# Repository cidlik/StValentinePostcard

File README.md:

# Идея

Сделать валентинку в виде печатной платы с микроконтроллером и светодиодами. Должна работать от
часовой батарейки. Основные пункты:

* должна быть дешевой;
* должно быть минимум компонентов (см. предыдущий пункт);
* должна быть низкопотребляющей;
* все компоненты, кроме светодиодов и кнопки, должны быть на обратной стороне платы.

Эскиз на рисунке ниже:

<figure style="text-align: center">
	
	<figcaption style="text-align: center">Эскиз устройства</figcaption>
</figure>

# Выбор светодиодов

Основные варианты:

* Обычные светодиоды, например, [TO-1608BC-MRE](https://www.chipdip.ru/product/to-1608bc-mre-svetodiod-krasnyy-smd-1608-112mkd-oasistek-9000414317):

    * (+) дешево
    * (+) энергоэффективно
    * (-) нужно много ног для управления
    * (-) сердито
    * Параметры:

        * Прямой ток 25 мА;
        * Прямое напряжение 2 В.

* Адресный, например, [SK(C)6812-RGBW-BW](https://www.chipdip.ru/product/sk-c-6812-rgbw-bw-neopixel-svetodiod-shenzhen-shiningled-9000373823):

    * (+) красиво, много режимов
    * (+) всего 2 провода для управления
    * (-) скорее всего будет больше жрать, хотя как запрограммировать
    * (-) борьба с наводками???
    * (-) дороже
    * Параметры:

        * Напряжение питания 3.7-5.5 В
        * Прямой ток 20-30 мА на один цвет.

# Оценка потребления

Выбираются 14 светодиодов TO-1608BC-MRE. Ток ограничивается до 15 мА через резистор. Режимы:

1. Один светодиод в единицу времени;
2. Все светодиоды разом (худший случай).

Для первого режима потребление по светодиодам 15 мА. Для второго - 15 * 14 = 210 мА.

Пусть будет _какая-то_ батарейка на 100 мАч (см. [таблицу](https://mosclock.ru/clock/o-garantii/zamena-batareek/tablitsa-sravneniya-chasovykh-batareek/?srsltid=AfmBOorHNBOLRriNnmurLrfbC0cLY0ivmhHh0GXlCDRKjwAtHPy7bsK3)). Тогда 

1. 100 / 15 ~= 6 ч на одни только светодиоды;
2. 100 / 210 ~= 0.5 ч на одни только светодиоды.

# Выбор микроконтроллера

Судя по всему, это будет STM32L0. Варианты:

1. [STM32L011F3P6](https://www.chipdip.ru/product/stm32l011f3p6-st-microelectronics-8003145100)
2. [STM32L010F4P6](https://www.chipdip.ru/product/stm32l010f4p6-mikrokontroller-arm-st-microelectronics-9001089803)

Почему STM:

* знаю, что там точно есть режимы с супер низким потреблением;
* знакомая платформа;
* не нужно будет докупать программатор, т.к. он есть.

Вариант 1:

* Корпус: TSSOP-20
* GPIO: 11-15 (зависит от того, что смогу сконфигурировать)
* Напряжение питания от 1.65 до 3.6 В.
* Тактирование от внутренней RC-цепочки.

Вариант 2 не рассматривается, т.к. 1-й вариант более чем устраивает.

# Что говорит ИИ?

* [Ответ 1](https://share.google/aimode/JZRhZsYDs94hqZSMV).
* [Ответ 2](https://share.google/aimode/ylKgjJaCaAhDsedJH).

# Выбор батарейки

Судя по всему, подходит [CR2032](https://www.dart.ru/cataloguenew/others/accumulator/html/cr2032.shtml).
Характеристики:

* выходное напряжение 3 В;
* выходной ток  0.4 мА;
* мощность 210 мА/ч.

# Блок-схема устройства

<figure style="text-align: center">
	
	<figcaption style="text-align: center">Блок-схема устройства</figcaption>
</figure>

# Попытка рассчитать буферный конденсатор

Потребляемая мощность:

$$ P = P_{mc} + P_d $$

где $P_{mc}$ - мощность, потребляемая МК, $P_d$ - мощность, рассеиваемая при зажигании одного
светодиода.

Требуется определить количество энергии, которое будет потреблено за 1 секунду. Оцениваем мощности:

* $ P_d = I^2 \cdot R = 0.015^2 \cdot 120 = 0.027 $ Вт;
* $ P_{mc} = 3 \cdot 0.0005 = 0.0015 $ Вт (грубая оценка, судя по всему не должно превышать этого значения, см.
"Table 22. Current consumption in Run mode, code with data processing running from Flash" для MSI
clock).

Тогда

$$ E = (0.027 + 0.0015) \cdot 1 = 0.0285\ Дж $$

Энергия конденсатора определяется выражением:

$$ E_c = {CU^2 \over 2} $$

Определяем разницу энергий - до включения светодиода и после выключения. Допустим, что напряжение
$U_{low}$ может упасть до 2 В. Эта разница - та энергия, которая уходит на микроконтроллер и на
горение светодиода. Тогда ёмкость:

$$ C = {2E \over U_0^2 - U_{low}^2} = {2 \cdot 0.0285 \over 3^2 - 2^2} = 0.0114\ Ф = 11400\ мкФ $$

Это при условии, что светодиод будет постоянно гореть, а микроконтроллер не будет переводиться в
низкопотребляющие режимы.

Пусть светодиод будет гореть 5% от всего времени, тогда $P_d = 0.027 \cdot 0.05 = 0.00135\ Вт$.
Тогда ёмкость:

$$ C = {2 \cdot (0.0015 + 0.00135) \over 3^2 - 2^2} = 1140\ мкФ$$

# Схема электрическая принципиальная

<figure style="text-align: center">
	
	<figcaption style="text-align: center">Схема электрическая принципиальная</figcaption>
</figure>

# Алгоритм сборки

* Пайка резисторов для светодиодов на нижней стороне платы: флюс, паста, установить резисторы,
  прогреть феном. После операции проверить мультиметром пайку (у каждого резистора есть переходное
  отверстие, использовать его и КП микроконтроллера).
  **Внимание!** R12 и R11 не запаивать!
* Пайка светодиодов на верхней стороне платы: флюс, паста, установить светодиоды, прогреть феном.
  После операции проверить мультиметром пайку (у каждого светодиода есть переходное отверстие,
  использовать его и землю).
* Пайка микроконтроллера: флюс, запаять паяльником краевые выводы. Затем движениями от МК до конца
  площадки нанести припой. После пайки проверить все линии. Проверить, нет ли КЗ по всем линиям.
* Запаять R15.
* Пайка кнопки. Кнопка размещается с верхней стороны. После установки в посадочное место обрезать
  выводы с другой стороны и запаять.
* Прошить МК прошивкой с флагом DEBUG, убедиться, что все ок.
* Прошить МК прошивкой без флага DEBUG.
* Запаять R12 и R11.
* Пайка конденсаторов (вывод с полосой - gnd). ~~Предположительно хватит 2-х конденсаторов~~
  Поставил все 3. Конденсаторы - с нижней стороны. После установки в посадочное   место обрезать
  выводы с другой стороны и запаять.
* Отчистить плату.
* Запаять отсек для батарейки и включить устройство.
* Зашкурить

# Итоговое потребление

* STATE_START: 380 мА (ничего не мигает)
* STATE_RUNNING_LED: 850 мА
* STATE_SYMMETRY_RUNNING_LED: 880 мА

Просадок напряжения питания осциллографом не увидел.

# Что можно улучшить?

## Конструктивно

* Вывести площадку с NRST, чтобы можно было не бояться закирпичить устройство.
* Добавить запаиваемую перемычку после R15, чтобы можно было более удобно измерять силу тока.
* Не забыть шелкографию при производстве плат))0))
* Выбрать какие-то другие светодиоды. Паять эти - сущий ад.

  * Возможно имеет смысл поставить низкопотребляющие светодиоды.

* Сделать площадки светодиодов и резисторов побольше чуть-чуть.
* Исправить посадочное место J1 - сейчас шаг маленький, не могу поставить стандартный PLS.
* Конденсатор после кнопки для фильтрации дребезга.
* Поставить запаиваемые перемычки на линиях LED10 и LED11, чтобы можно было паять сразу все резисторы. Тогда проблем с прошивкой быть не должно.

## Программно

* Улучшить реализацию фильтра дребезга.
* Добавить больше режимов.
* Поддержать Stop и Standby режимы.
* Более тонко понастраивать потребление через задержки.
* Использовать LSI вместо HSI16.

# Итоги

* Устройство заработало.

<figure style="text-align: center">
	
	<figcaption style="text-align: center">Результат. Передняя сторона</figcaption>
</figure>

<figure style="text-align: center">
	
	<figcaption style="text-align: center">Результат. Задняя сторона</figcaption>
</figure>

<figure style="text-align: center">
	
	<figcaption style="text-align: center">Результат в действии</figcaption>
</figure>

* Дешевым проект не назову - платы дорого вышли. Но делал срочный заказ, чтобы успеть к сроку, так
  что пойдет.

* Требование по низкому потреблению выдержано, можно улучшить.

# Для справки

* Светодиоды с низким током потребления:

    * [led smd 1ma](https://www.chipdip.ru/search?searchtext=led+smd+1ma)
    * [VLMA3100-GS08](https://www.chipdip.ru/product/vlma3100-gs08-led-yellow-smd-plcc-2-2-ma-2.2-v-594-vishay-8733971327)

# Полезные ссылки

* [Basics of power supply design for MCU](https://wiki.st.com/stm32mcu/wiki/Basics_of_power_supply_design_for_MCU)
* [Краткое руководство KiCad](https://docs.kicad.org/5.1/ru/getting_started_in_kicad/getting_started_in_kicad.html)
* [Ultra Low Power LED Flasher using the Padauk PFS154](https://cpldcpu.com/2021/02/07/ultra-low-power-led-flasher/)
* [Про буферные конденсаторы](https://habr.com/ru/articles/671232/)

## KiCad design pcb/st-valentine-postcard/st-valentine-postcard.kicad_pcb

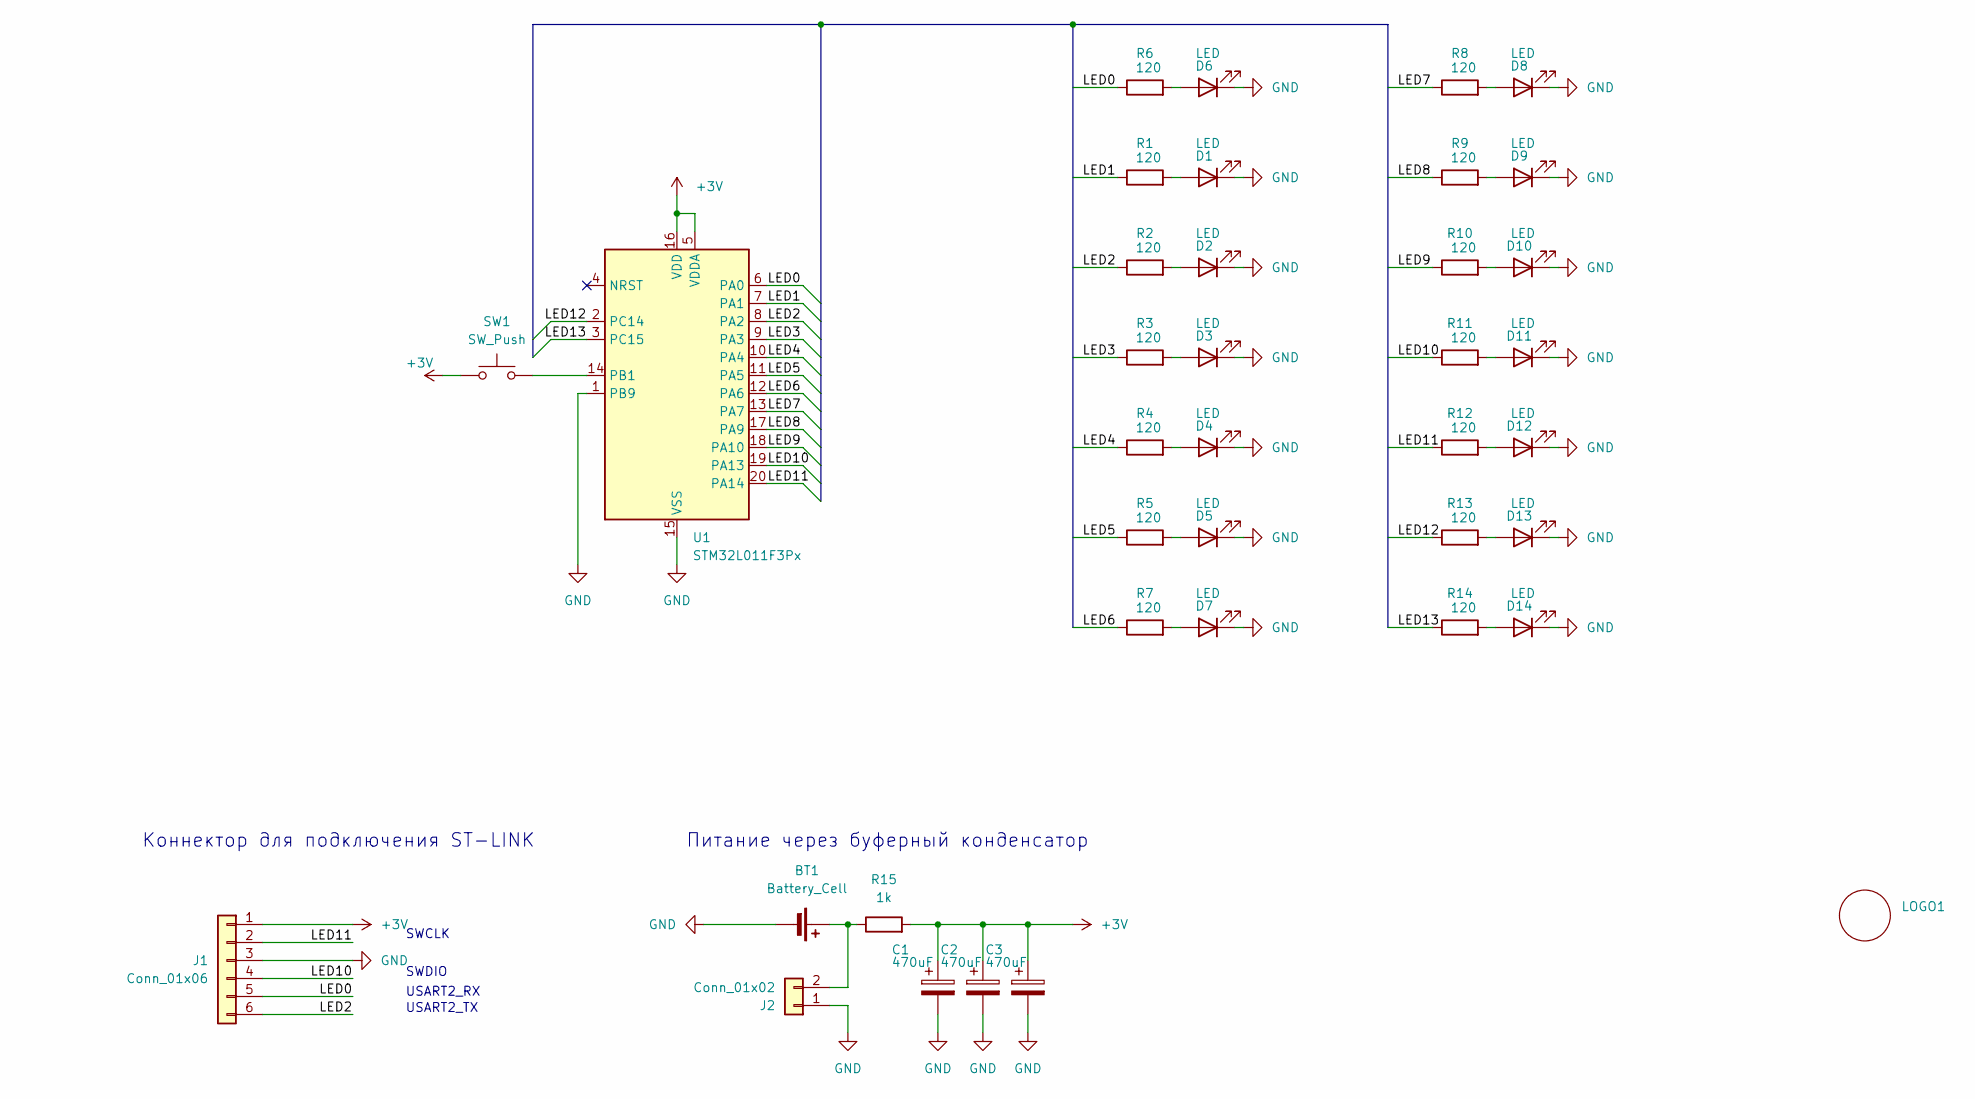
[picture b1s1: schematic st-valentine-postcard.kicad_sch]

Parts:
BT1: Battery_Cell; BatteryHolder_KLS5_CR2032_01
C1, C2, C3: 470uF; C_Radial_D6.3mm_H7.0mm_P2.50mm
D1, D2, D3, D4, D5, D6, D7, D8, D9, D10, D11, D12, D13, D14: LED; D_0201_0603Metric
J1: Conn_01x06; PinHeader_1x06_P2.00mm_Vertical
J2: Conn_01x02; PinHeader_1x02_P2.54mm_Vertical
LOGO1: cdk_logo_6x6mm
R1, R2, R3, R4, R5, R6, R7, R8, R9, R10, R11, R12, R13, R14: 120; R_0201_0603Metric_1.6x0.8
R15: 1k; R_0201_0603Metric_1.6x0.8
SW1: SW_Push; SW_PUSH_6mm_H4.3mm
U1: STM32L011F3Px; TSSOP-20_4.4x6.5mm_P0.65mm

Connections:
+3V: C1.1, C2.1, C3.1, J1.1, R15.2, SW1.1, U1.5 (VDDA), U1.16 (VDD)
/LED0: J1.5, R6.1, U1.6 (PA0)
/LED1: R1.1, U1.7 (PA1)
/LED2: J1.6, R2.1, U1.8 (PA2)
/LED3: R3.1, U1.9 (PA3)
/LED4: R4.1, U1.10 (PA4)
/LED5: R5.1, U1.11 (PA5)
/LED6: R7.1, U1.12 (PA6)
/LED7: R8.1, U1.13 (PA7)
/LED8: R9.1, U1.17 (PA9)
/LED9: R10.1, U1.18 (PA10)
/LED10: J1.4, R11.1, U1.19 (PA13)
/LED11: J1.2, R12.1, U1.20 (PA14)
/LED12: R13.1, U1.2 (PC14)
/LED13: R14.1, U1.3 (PC15)
GND: BT1.2 (-), C1.2, C2.2, C3.2, D1.1 (K), D2.1 (K), D3.1 (K), D4.1 (K), D5.1 (K), D6.1 (K), D7.1 (K), D8.1 (K), D9.1 (K), D10.1 (K), D11.1 (K), D12.1 (K), D13.1 (K), D14.1 (K), J1.3, J2.1, U1.1 (PB9), U1.15 (VSS)
unnamed: BT1.1 (+), J2.2, R15.1
unnamed: D1.2 (A), R1.2
unnamed: D2.2 (A), R2.2
unnamed: D3.2 (A), R3.2
unnamed: D4.2 (A), R4.2
unnamed: D5.2 (A), R5.2
unnamed: D6.2 (A), R6.2
unnamed: D7.2 (A), R7.2
unnamed: D8.2 (A), R8.2
unnamed: D9.2 (A), R9.2
unnamed: D10.2 (A), R10.2
unnamed: D11.2 (A), R11.2
unnamed: D12.2 (A), R12.2
unnamed: D13.2 (A), R13.2
unnamed: D14.2 (A), R14.2
unnamed: SW1.2, U1.14 (PB1)

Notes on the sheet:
USART2_TX
Коннектор для подключения ST-LINK
SWDIO
USART2_RX
SWCLK
Питание через буферный конденсатор

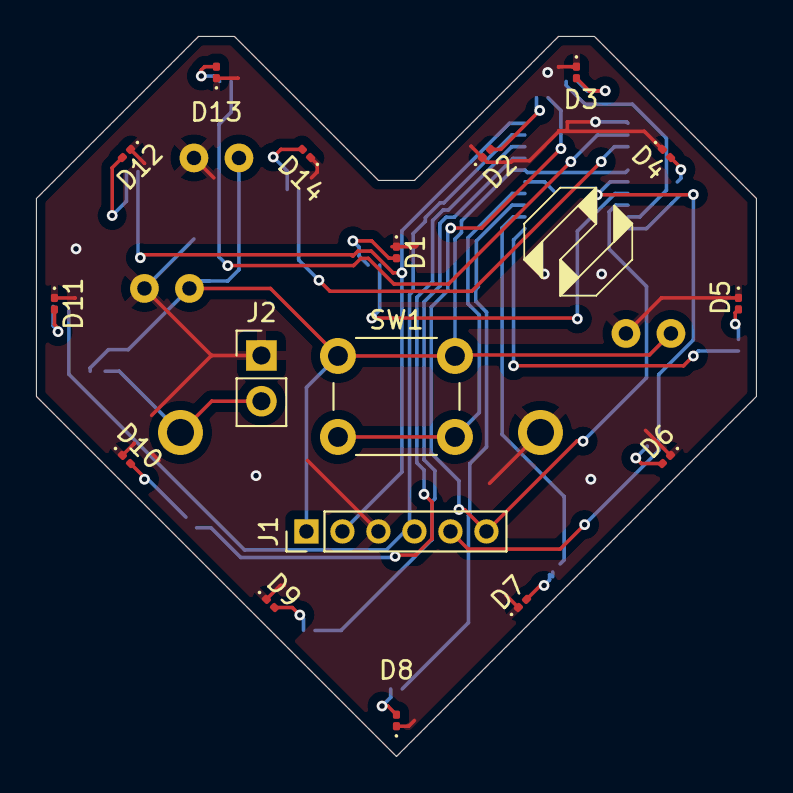
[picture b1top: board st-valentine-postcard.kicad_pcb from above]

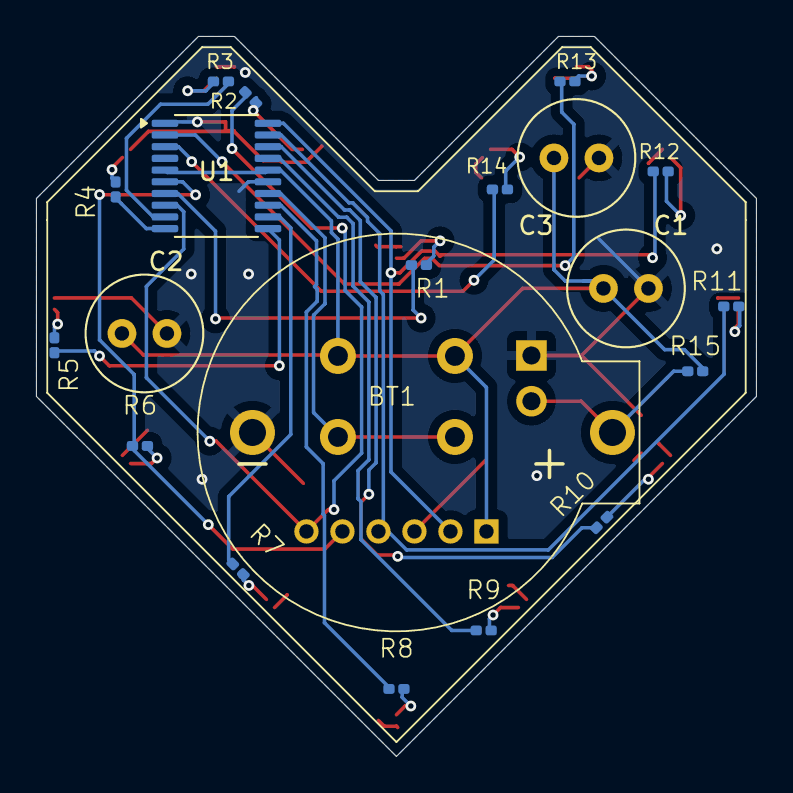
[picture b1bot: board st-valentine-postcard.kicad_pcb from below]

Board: 2 copper layers, 40.0 x 40.0 mm, 38 parts (20 on the bottom side), 32 nets.

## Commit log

2026-01-31 Fix README misprint
2026-01-31 README: Update document
